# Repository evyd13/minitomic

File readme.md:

# Minitomic
Use latest KiCAD nightly for the PCB files

PCB designed in KiCAD  
Plate designed in FreeCAD  
Case designed in Fusion360

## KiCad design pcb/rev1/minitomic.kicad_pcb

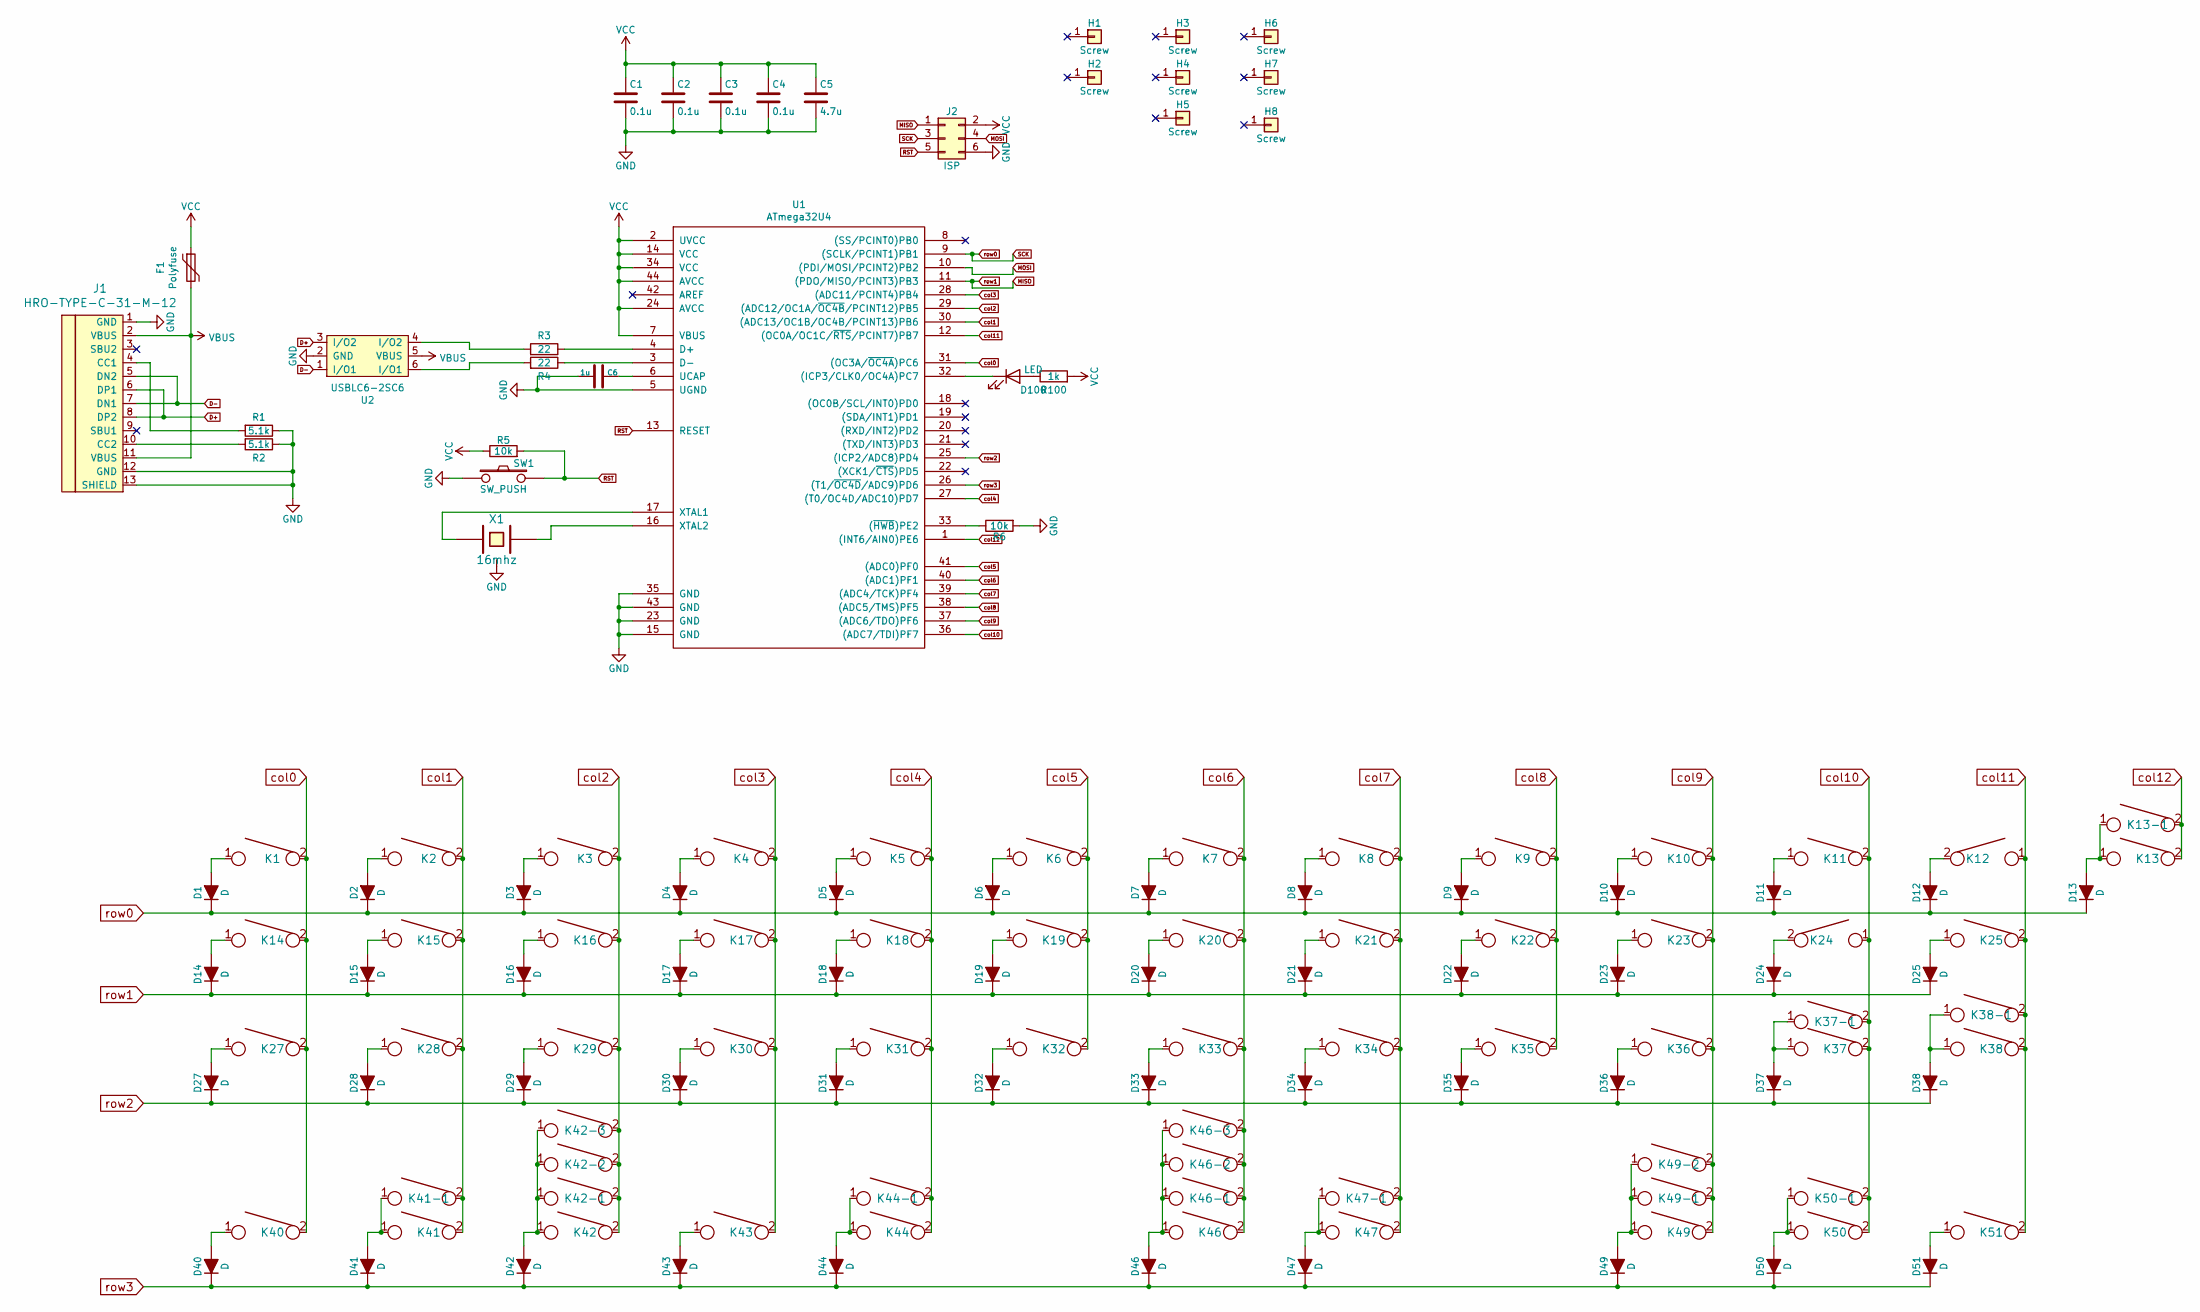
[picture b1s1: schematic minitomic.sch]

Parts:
C1, C2, C3, C4: 0.1u; C_0603
C5: 4.7u; C_0805
C6: 1u; C_0603
D1, D2, D3, D4, D5, D6, D7, D8, D9, D10, D11, D12, D13, D14, D15, D16, D17, D18, D19, D20, D21, D22, D23, D24, D25, D27, D28, D29, D30, D31, D32, D33, D34, D35, D36, D37, D38, D40, D41, D42, D43, D44, D46, D47, D49, D50, D51: D; D_0805
D100: LED; LED_0805
F1: Polyfuse; R_0805
H1, H2, H3, H4, H5, H6, H7, H8: Screw; 2mm_hole
J1: HRO-TYPE-C-31-M-12
J2: ISP; isp_standard
K1, K2, K3, K4, K5, K6, K7, K8, K9, K10, K11, K12, K13, K15, K16, K17, K18, K19, K20, K21, K22, K23, K24, K28, K29, K30, K31, K32, K33, K34, K35, K36, K37, K38-1, K41-1, K42, K42-2, K43, K47, K47-1, K49-1, K49-2, K50-1: KEYSW; CHERRY_PLATE_100H
K13-1: KEYSW; CHERRY_PCB_200H
K14, K37-1, K38, K40, K41, K42-1, K42-3, K49, K50, K51: KEYSW; CHERRY_PLATE_125H
K25, K27, K44: KEYSW; CHERRY_PLATE_175H
K44-1: KEYSW; CHERRY_PCB_225H_F
K46: KEYSW; CHERRY_PCB_200H_F
K46-1: KEYSW; CHERRY_PCB_700H_F
K46-2: KEYSW; CHERRY_PCB_625H_F
K46-3: KEYSW; CHERRY_PCB_275H_F
R1, R2: 5.1k; R_0603
R3, R4: 22; R_0603
R5, R6: 10k; R_0603
R100: 1k; R_0805
SW1: SW_PUSH; SW_SPST_TL3342
U1: ATmega32U4; ATMEGA32U4
U2: USBLC6-2SC6
X1: 16mhz; Resonator_SMD_muRata_CSTNExxV-3Pin-p1.2

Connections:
D+: J1.6 (DP1), J1.8 (DP2), U2.3 (I/O2)
D-: J1.5 (DN2), J1.7 (DN1), U2.1 (I/O1)
GND: C1.2, C2.2, C3.2, C4.2, C5.2, C6.2, J1.1 (GND), J1.12 (GND), J1.13 (SHIELD), J2.6, R1.1, R2.1, R6.2, SW1.1, U1.5 (UGND), U1.15 (GND), U1.23 (GND), U1.35 (GND), U1.43 (GND), U2.2 (GND), X1.3
MISO: D14.1 (K), D15.1 (K), D16.1 (K), D17.1 (K), D18.1 (K), D19.1 (K), D20.1 (K), D21.1 (K), D22.1 (K), D23.1 (K), D24.1 (K), D25.1 (K), J2.1, U1.11 ((PDO/MISO/PCINT3)PB3)
MOSI: J2.4, U1.10 ((PDI/MOSI/PCINT2)PB2)
unnamed: C6.1, U1.6 (UCAP)
unnamed: D1.2 (A), K1.1
unnamed: D2.2 (A), K2.1
unnamed: D3.2 (A), K3.1
unnamed: D4.2 (A), K4.1
unnamed: D5.2 (A), K5.1
unnamed: D6.2 (A), K6.1
unnamed: D7.2 (A), K7.1
unnamed: D8.2 (A), K8.1
unnamed: D9.2 (A), K9.1
unnamed: D10.2 (A), K10.1
unnamed: D11.2 (A), K11.1
unnamed: D12.2 (A), K12.2
unnamed: D13.2 (A), K13.1, K13-1.1
unnamed: D14.2 (A), K14.1
unnamed: D15.2 (A), K15.1
unnamed: D16.2 (A), K16.1
unnamed: D17.2 (A), K17.1
unnamed: D18.2 (A), K18.1
unnamed: D19.2 (A), K19.1
unnamed: D20.2 (A), K20.1
unnamed: D21.2 (A), K21.1
unnamed: D22.2 (A), K22.1
unnamed: D23.2 (A), K23.1
unnamed: D24.2 (A), K24.2
unnamed: D25.2 (A), K25.1
unnamed: D27.2 (A), K27.1
unnamed: D28.2 (A), K28.1
unnamed: D29.2 (A), K29.1
unnamed: D30.2 (A), K30.1
unnamed: D31.2 (A), K31.1
unnamed: D32.2 (A), K32.1
unnamed: D33.2 (A), K33.1
unnamed: D34.2 (A), K34.1
unnamed: D35.2 (A), K35.1
unnamed: D36.2 (A), K36.1
unnamed: D37.2 (A), K37.1, K37-1.1
unnamed: D38.2 (A), K38.1, K38-1.1
unnamed: D40.2 (A), K40.1
unnamed: D41.2 (A), K41.1, K41-1.1
unnamed: D42.2 (A), K42.1, K42-1.1, K42-2.1, K42-3.1
unnamed: D43.2 (A), K43.1
unnamed: D44.2 (A), K44.1, K44-1.1
unnamed: D46.2 (A), K46.1, K46-1.1, K46-2.1, K46-3.1
unnamed: D47.2 (A), K47.1, K47-1.1
unnamed: D49.2 (A), K49.1, K49-1.1, K49-2.1
unnamed: D50.2 (A), K50.1, K50-1.1
unnamed: D51.2 (A), K51.1
unnamed: D100.1 (K), U1.32 ((ICP3/CLK0/OC4A)PC7)
unnamed: D100.2 (A), R100.1
unnamed: J1.4 (CC1), R1.2
unnamed: J1.10 (CC2), R2.2
unnamed: R3.1, U1.4 (D+)
unnamed: R3.2, U2.4 (I/O2)
unnamed: R4.1, U1.3 (D-)
unnamed: R4.2, U2.6 (I/O1)
unnamed: R6.1, U1.33 ((~HWB~)PE2)
unnamed: U1.16 (XTAL2), X1.2
unnamed: U1.17 (XTAL1), X1.1
RST: J2.5, R5.2, SW1.2, U1.13 (RESET)
SCK: D1.1 (K), D2.1 (K), D3.1 (K), D4.1 (K), D5.1 (K), D6.1 (K), D7.1 (K), D8.1 (K), D9.1 (K), D10.1 (K), D11.1 (K), D12.1 (K), D13.1 (K), J2.3, U1.9 ((SCLK/PCINT1)PB1)
VBUS: F1.2, J1.2 (VBUS), J1.11 (VBUS), U2.5 (VBUS)
VCC: C1.1, C2.1, C3.1, C4.1, C5.1, F1.1, J2.2, R5.1, R100.2, U1.2 (UVCC), U1.7 (VBUS), U1.14 (VCC), U1.24 (AVCC), U1.34 (VCC), U1.44 (AVCC)
col0: K1.2, K14.2, K27.2, K40.2, U1.31 ((OC3A/~OC4A~)PC6)
col1: K2.2, K15.2, K28.2, K41.2, K41-1.2, U1.30 ((ADC13/OC1B/OC4B/PCINT13)PB6)
col2: K3.2, K16.2, K29.2, K42.2, K42-1.2, K42-2.2, K42-3.2, U1.29 ((ADC12/OC1A/~OC4B~/PCINT12)PB5)
col3: K4.2, K17.2, K30.2, K43.2, U1.28 ((ADC11/PCINT4)PB4)
col4: K5.2, K18.2, K31.2, K44.2, K44-1.2, U1.27 ((T0/OC4D/ADC10)PD7)
col5: K6.2, K19.2, K32.2, U1.41 ((ADC0)PF0)
col6: K7.2, K20.2, K33.2, K46.2, K46-1.2, K46-2.2, K46-3.2, U1.40 ((ADC1)PF1)
col7: K8.2, K21.2, K34.2, K47.2, K47-1.2, U1.39 ((ADC4/TCK)PF4)
col8: K9.2, K22.2, K35.2, U1.38 ((ADC5/TMS)PF5)
col9: K10.2, K23.2, K36.2, K49.2, K49-1.2, K49-2.2, U1.37 ((ADC6/TDO)PF6)
col10: K11.2, K24.1, K37.2, K37-1.2, K50.2, K50-1.2, U1.36 ((ADC7/TDI)PF7)
col11: K12.1, K25.2, K38.2, K38-1.2, K51.2, U1.12 ((OC0A/OC1C/~RTS~/PCINT7)PB7)
col12: K13.2, K13-1.2, U1.1 ((INT6/AIN0)PE6)
row2: D27.1 (K), D28.1 (K), D29.1 (K), D30.1 (K), D31.1 (K), D32.1 (K), D33.1 (K), D34.1 (K), D35.1 (K), D36.1 (K), D37.1 (K), D38.1 (K), U1.25 ((ICP2/ADC8)PD4)
row3: D40.1 (K), D41.1 (K), D42.1 (K), D43.1 (K), D44.1 (K), D46.1 (K), D47.1 (K), D49.1 (K), D50.1 (K), D51.1 (K), U1.26 ((T1/~OC4D~/ADC9)PD6)

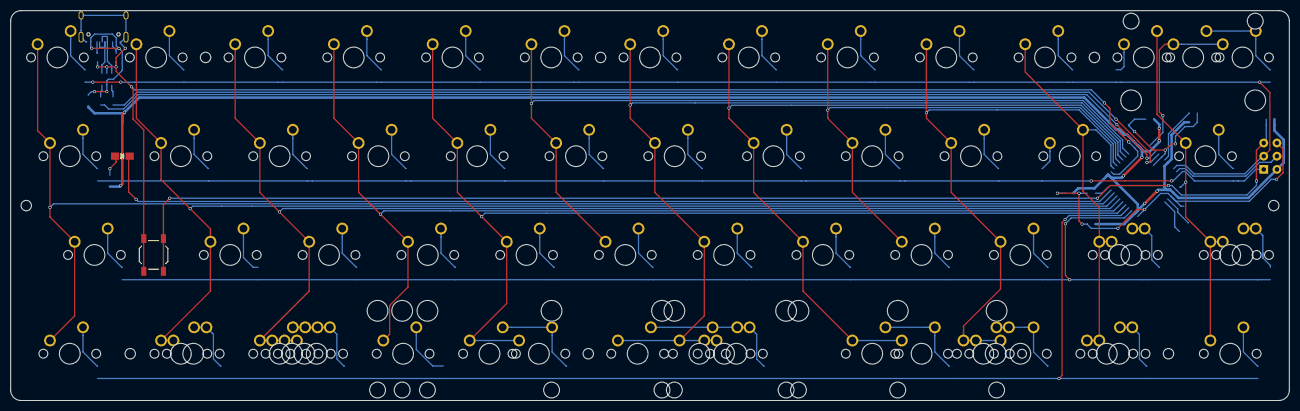
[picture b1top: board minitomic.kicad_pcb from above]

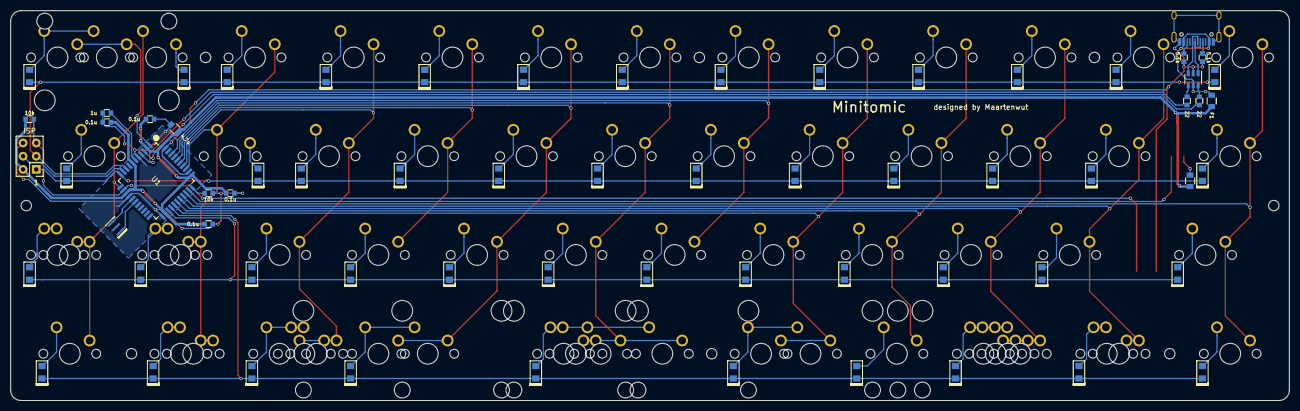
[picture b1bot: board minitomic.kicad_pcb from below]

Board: 2 copper layers, 246.0 x 75.0 mm, 138 parts (66 on the bottom side), 83 nets.

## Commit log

2020-04-11 Upload files
